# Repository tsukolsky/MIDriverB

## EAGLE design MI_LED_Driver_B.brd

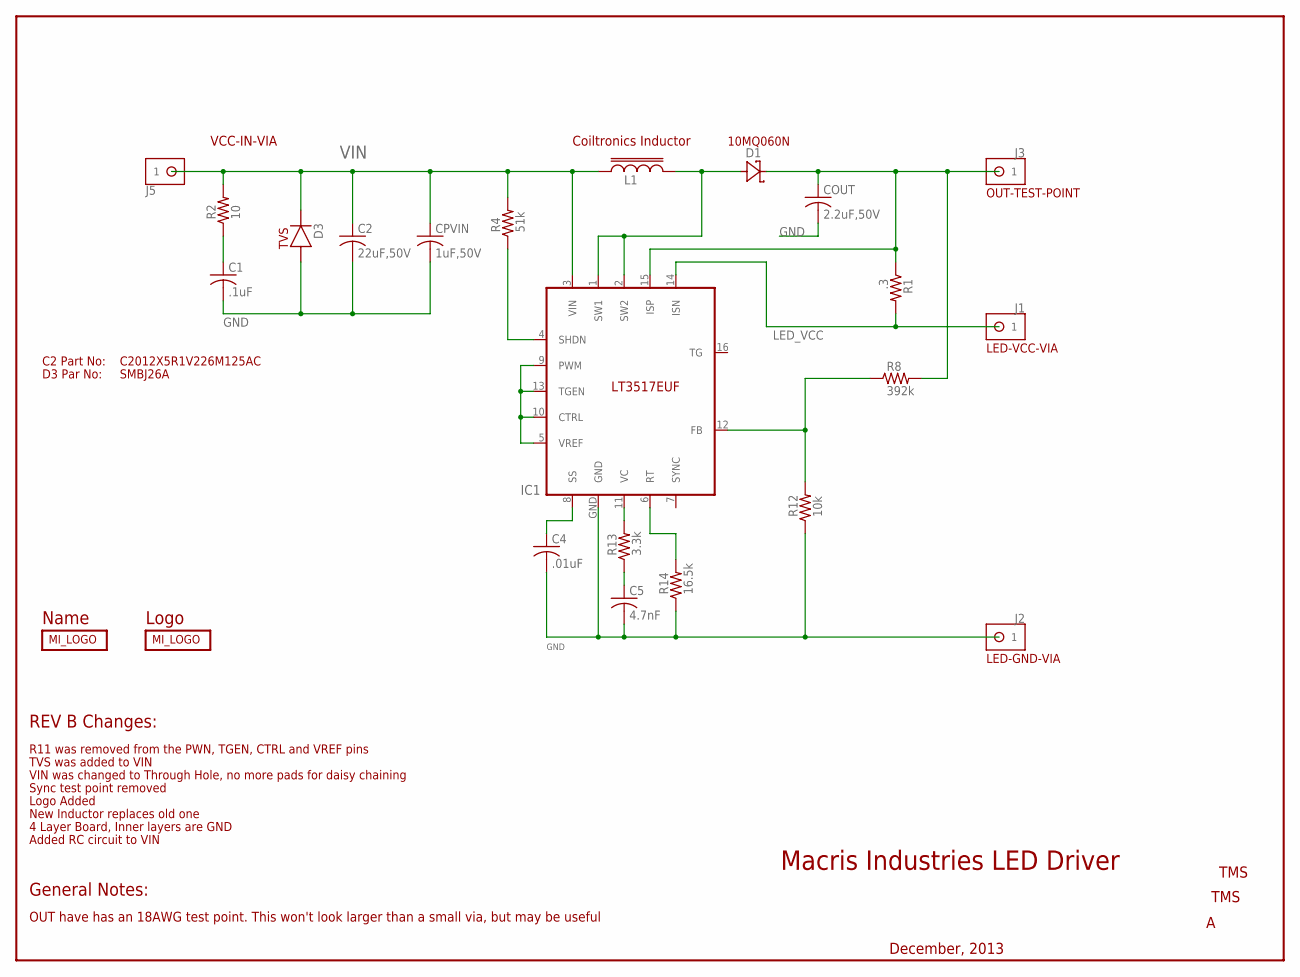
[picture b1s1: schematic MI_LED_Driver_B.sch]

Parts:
C1: .1uF; C0805
C2: 22uF,50V; C0805
C4: .01uF; C0805
C5: 4.7nF; C0805
COUT: 2.2uF,50V; C1206
CPVIN: 1uF,50V; C1206
D1: SCHOTTKY-DO-213AC-2; DO-213AC-2
D3: DIODE-DO-214AA; DO-214AA
IC1: LT3517; QFN_SM
J1, J2, J5: HDR-1X1-14AWG; 14AWG-SOLDERPOINT
J3: HDR-1X1-18AWG_WIRE; 18AWG-SOLDERPOINT
L1: IND-COILTRONICS-MPI4040; IND-COILTRONICS
R1: .3; R1206
R2: 10; R0805
R4: 51k; R0805
R8: 392k; R0805
R12: 10k; R0805
R13: 3.3k; R0805
R14: 16.5k; R0805
U$1: MI_LOGO-NAME_ONE; MI_LOGO_NAME_1
U$2: MI_LOGO-ONE; MI_LOGO

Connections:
GND: C1.2, C2.2, C4.2, C5.2, COUT.2, CPVIN.2, D3.ANODE (A), IC1.GND, J2.P$1, R12.1, R14.1
LED_VCC: IC1.14 (ISN), J1.P$1, R1.2
unnamed: IC1.4 (SHDN), R4.1
unnamed: IC1.5 (VREF), IC1.9 (PWM), IC1.10 (CTRL), IC1.13 (TGEN)
unnamed: C4.1, IC1.8 (SS)
unnamed: IC1.12 (FB), R8.1, R12.2
unnamed: D1.A, IC1.1 (SW1), IC1.2 (SW2), L1.NO_DOT (2)
unnamed: C5.1, R13.1
unnamed: IC1.11 (VC), R13.2
unnamed: IC1.6 (RT), R14.2
unnamed: C1.1, R2.1
unnamed: COUT.1, D1.C, IC1.15 (ISP), J3.1, R1.1, R8.2
VIN: C2.1, CPVIN.1, D3.CATH (C), IC1.3 (VIN), J5.P$1, L1.DOT (1), R2.2, R4.2

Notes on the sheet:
TMS
Macris Industries LED Driver
December, 2013
10MQ060N
LED-GND-VIA
LED-VCC-VIA
OUT-TEST-POINT
General Notes:
OUT have has an 18AWG test point. This won't look larger than a small via, but may be useful
VCC-IN-VIA
Coiltronics Inductor
REV B Changes:
R11 was removed from the PWN, TGEN, CTRL and VREF pins
TVS was added to VIN
VIN was changed to Through Hole, no more pads for daisy chaining
Sync test point removed
Logo Added
New Inductor replaces old one
4 Layer Board, Inner layers are GND
Name
Logo
SMBJ26A
TVS
C2012X5R1V226M125AC
C2 Part No:
Added RC circuit to VIN
D3 Par No:

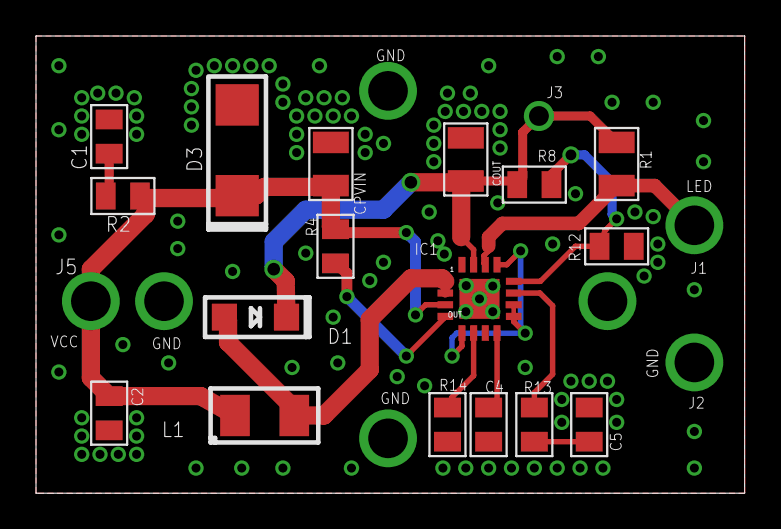
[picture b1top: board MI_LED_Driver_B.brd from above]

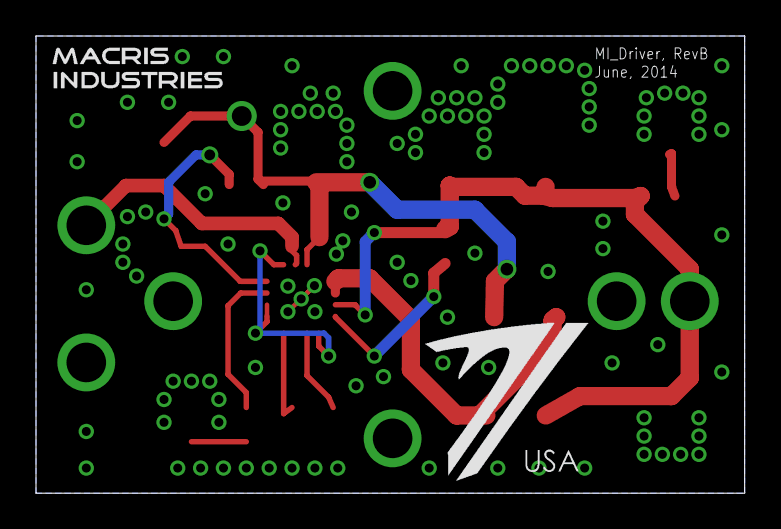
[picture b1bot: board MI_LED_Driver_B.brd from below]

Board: 2 copper layers, 39.4 x 25.4 mm, 23 parts (2 on the bottom side), 13 nets.

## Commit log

2014-05-26 Finished with prelim re-route and update to board with updated parts (RC circuit, TVS), C2. Not four layers yet, also probably getting a via put in again.
2014-06-11 Finished with new board, larger and should dissipate heat better.
2014-07-29 Updated eagle.epf??? Doesnt mean anything really
2014-10-22 Updates for IDK what
2014-10-22 Upudated with 805 chip sizes
2014-10-23 Updates with correct part sizes
